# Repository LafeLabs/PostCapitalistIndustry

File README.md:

#   Theory and Practice of Trash Magic

### Lafe Spietz 2016

[Intellectual Property Notice("license")](intellectual_property_notice.md)

[Bibliography](bibliography.md)

[Funding Proposal](heilmeier_catechism_lafelabs.md)

[Demo List](demo_list.md)

[Glossary List](glossary_terms.md)

[Format Notes](format_notes.md)

[Technical Roadmap](technical_roadmap.md)

[Purpose of Book 1](purpose_book1.md)

[Illustrations for Book I](illustrations_for_book_i.md)

[3d files for volume 1 ](3dfilesVolume1List.md)

[videos for volume 1 ](videos.md)

### Book 1. Philosophy of Trash Magic: Ways of Witchery and Wizardry

1. [What is capitalism?](capitalism.md)
2. [What is free technology?](free_technology.md) 
3. [Statement of Principles](Principles.md)
4. [What is Trash Magic?](what_is_the_trash_wizard.md)
5. [taking over the universities](universities.md)
6. [Rumbles of Robots](RumblesRobots.md)
7. [Free Drugs, SlimeZistors, and Ion Magic](slimeTechPolitical.md)
8. [Magic Tales and Magic Lore](value_circles_economics.md)
9. [The Great Junk Car Feed](JunkCars.md)
10. [Factories Everywhere and Nowhere](means_of_production.md) 
11. [Visions of a Better Tomorrow](visions.md)
12. [Free Everything](problems.md)
13. [Techniques](techniquesBook1.md)
14. [Let's Build This!](lets_build.md)
 
[Appendix: The Fourteen Contemplations of Manifesto](contemplations.md)

### Book 2. The Practice of Trash Magic: the Stickening

[book 2 summary](book2summary.md)

1. [Post Capitalist Industry: Trash Magic](capitalism_technical.md)
2. [Measuring the post capitalist world](Measures.md)
3. [Fear and loathing in the vector fields](Fields.md)
4. [Coils for Magnets and Motors](coils_for_magnets_and_motors.md)
5. [Motors and Pumps](MotorsPumps.md)
6. [3d Circuit Fabrication Technology from Trash](circuit_fabrication_technology.md)
7. [Rumbles of Robots](RumblesRobots.md)
8. [Energy](Energy.md) 
9. [Resonance](Resonance.md)
10. [Skeletron](skeletron.md)
11.  [Fractal Reactors and the SlimeZistor](FractalReactorSlimeZistor.md)
12. [Supply chain data structures, call to action](data_structures.md)

## Other media, volume I only

1. 3d files for each chapter, with a VR fly thru, and 3d printer files and photos with paint, also made without 3d printers(mine are hand made)
2. videos for each chapter
3. all illustrations are coloring book images
4. artifacts distributed with the book
5. documentation for tale and lore for artifacts: noise stick, vibration stick, whirligig USB charger
6. hard cover made from soft cover by hand using trash, with magic integrated into cover, fiction chapter and university chapter will have user submitted versions in different copies, there will be local variations in these.

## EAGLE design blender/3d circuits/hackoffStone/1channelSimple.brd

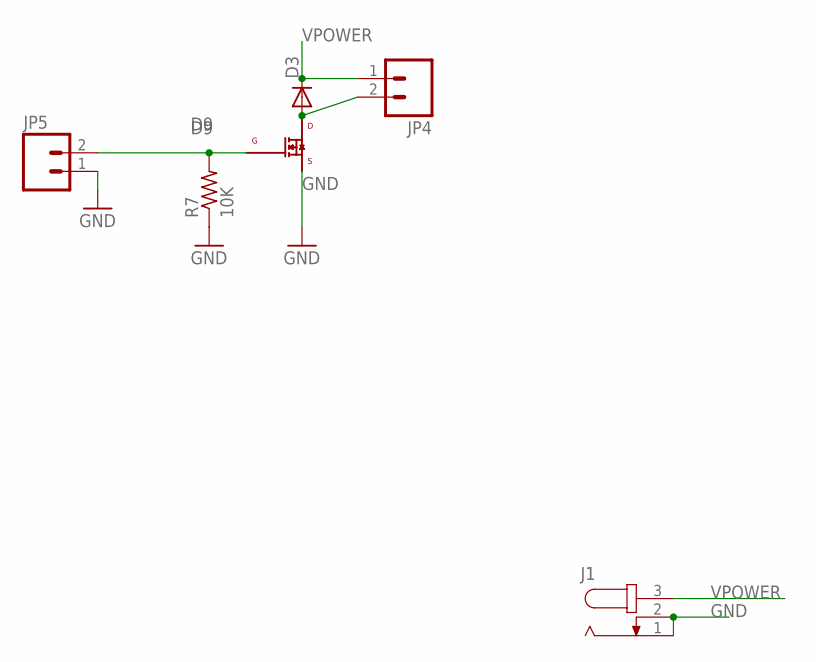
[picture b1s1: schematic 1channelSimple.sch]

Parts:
D3: DIODE-DO-214AC; DO-214AC
J1: JACK-PLUG1; SPC4078
JP4, JP5: M02PTH; 1X02
Q3: IRLML0060; SOT-23
R7: 10K; R0603

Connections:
D9: JP5.2, Q3.1 (GATE), R7.2
GND: J1.1, J1.2, JP5.1, Q3.2 (SOURCE), R7.1
unnamed: D3.A, JP4.2, Q3.3 (DRAIN)
VPOWER: D3.C, J1.3, JP4.1

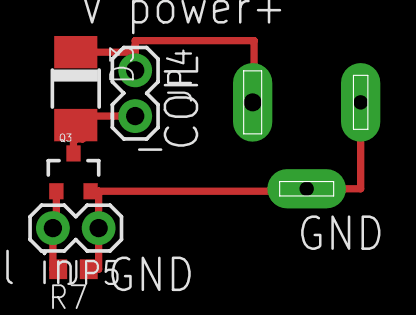
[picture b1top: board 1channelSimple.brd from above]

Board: 2 copper layers, 6 parts (1 on the bottom side), 4 nets.

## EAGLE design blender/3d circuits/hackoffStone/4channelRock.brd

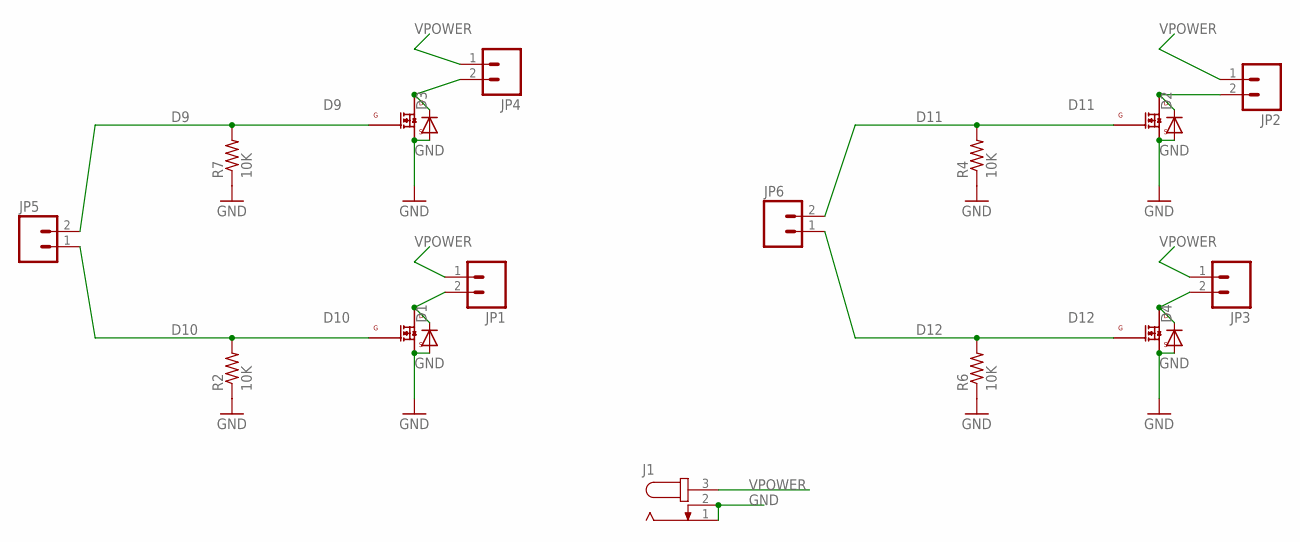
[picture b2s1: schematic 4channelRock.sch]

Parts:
D1, D2, D3, D4: DIODE-DO-214AC; DO-214AC
J1: JACK-PLUG1; SPC4078
JP1, JP2, JP3, JP4, JP5, JP6: M02PTH; 1X02
Q1, Q2, Q3, Q4: IRLML0060; SOT-23
R2, R4, R6, R7: 10K; R0603

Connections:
D9: JP5.2, Q3.1 (GATE), R7.2
D10: JP5.1, Q1.1 (GATE), R2.2
D11: JP6.2, Q2.1 (GATE), R4.2
D12: JP6.1, Q4.1 (GATE), R6.2
GND: D1.A, D2.A, D3.A, D4.A, J1.1, J1.2, Q1.2 (SOURCE), Q2.2 (SOURCE), Q3.2 (SOURCE), Q4.2 (SOURCE), R2.1, R4.1, R6.1, R7.1
unnamed: D3.C, JP4.2, Q3.3 (DRAIN)
unnamed: D1.C, JP1.2, Q1.3 (DRAIN)
unnamed: D2.C, JP2.2, Q2.3 (DRAIN)
unnamed: D4.C, JP3.2, Q4.3 (DRAIN)
VPOWER: J1.3, JP1.1, JP2.1, JP3.1, JP4.1

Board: 2 copper layers, 19 parts (0 on the bottom side), 10 nets, no tracks yet.

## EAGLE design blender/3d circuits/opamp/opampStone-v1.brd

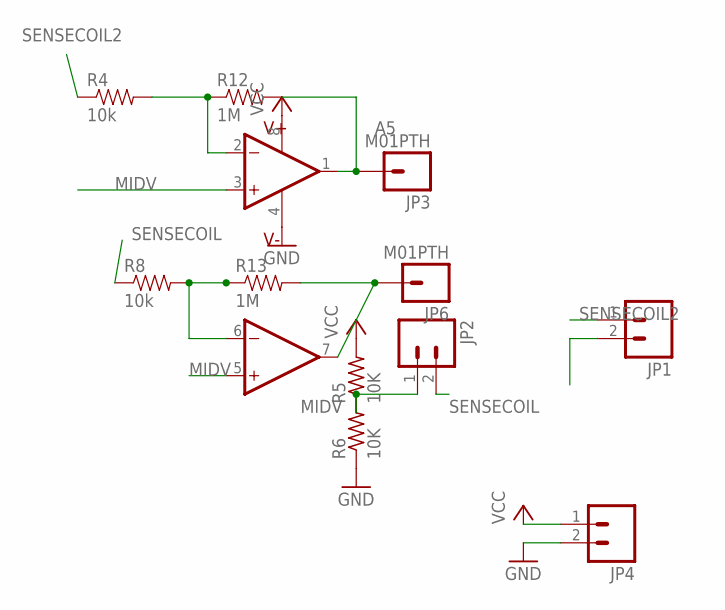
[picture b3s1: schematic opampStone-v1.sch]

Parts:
JP1, JP2, JP4: M02PTH; 1X02
JP3, JP6: M01PTH; 1X01
R4, R8: 10k; 0603-RES
R5, R6: 10K; R0603
R12, R13: 1M; 0805
U2: MCP6242; 8-SOIC

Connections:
A4: JP6.1, R13.2, U2.7 (OUTB)
A5: JP3.1, R12.2, U2.1 (OUTA)
GND: JP4.2, R6.1, U2.4 (V-)
MIDV: JP1.2, JP2.1, R5.1, R6.2, U2.3 (+INA), U2.5 (+INB)
unnamed: R4.2, R12.1, U2.2 (-INA)
unnamed: R8.2, R13.1, U2.6 (-INB)
SENSECOIL: JP2.2, R8.1
SENSECOIL2: JP1.1, R4.1
VCC: JP4.1, R5.2, U2.8 (V+)

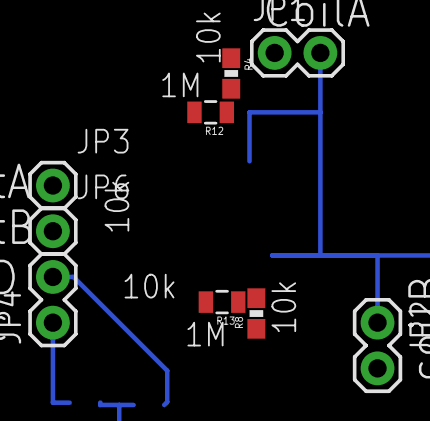
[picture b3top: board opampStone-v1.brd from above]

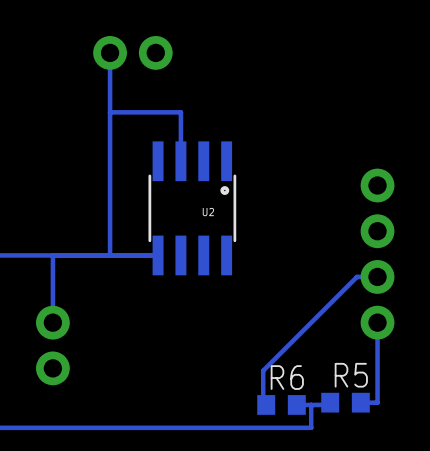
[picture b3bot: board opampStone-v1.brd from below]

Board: 2 copper layers, 12 parts (3 on the bottom side), 9 nets.

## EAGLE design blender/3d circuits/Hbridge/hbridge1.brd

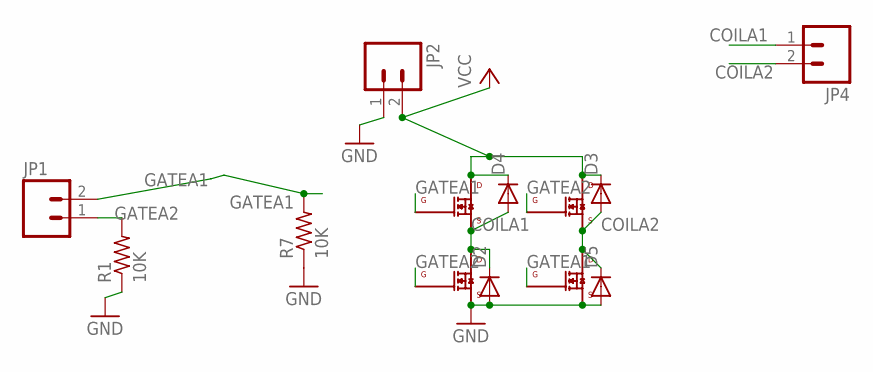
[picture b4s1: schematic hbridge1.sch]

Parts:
D2, D3, D4, D5: DIODE-DO-214AC; DO-214AC
JP1, JP2, JP4: M02PTH; 1X02
Q2, Q3, Q4, Q5: IRLML0060; SOT-23
R1, R7: 10K; R0603

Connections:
COILA1: D2.C, D4.A, JP4.1, Q2.3 (DRAIN), Q4.2 (SOURCE)
COILA2: D3.A, D5.C, JP4.2, Q3.2 (SOURCE), Q5.3 (DRAIN)
GATEA1: JP1.2, Q4.1 (GATE), Q5.1 (GATE), R7.2
GATEA2: JP1.1, Q2.1 (GATE), Q3.1 (GATE), R1.2
GND: D2.A, D5.A, JP2.1, Q2.2 (SOURCE), Q5.2 (SOURCE), R1.1, R7.1
VCC: D3.C, D4.C, JP2.2, Q3.3 (DRAIN), Q4.3 (DRAIN)

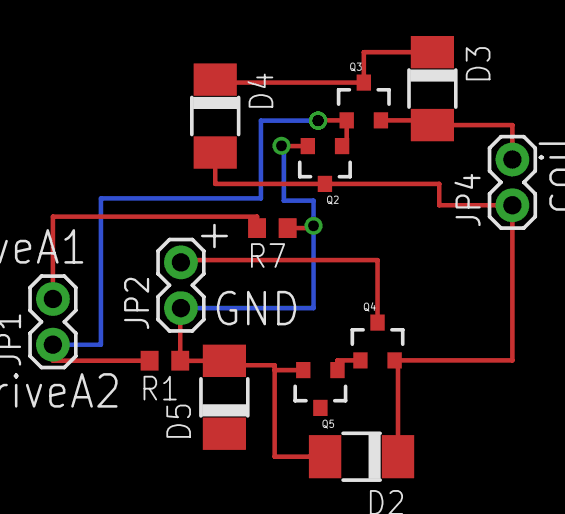
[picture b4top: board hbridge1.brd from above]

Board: 2 copper layers, 13 parts (0 on the bottom side), 6 nets.

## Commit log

2016-02-04 Update README.md
    add table of contents, with link to first chapter
2016-02-04 Update README.md
    capitalization of capitalism
2016-02-04 Moved all the python notebooks over
    from the cloud drive to the desktop git folder, trying to do this git
    thing again for real
2016-02-04 added cut and paste to capitalism chapter
2016-02-04 Rename Filelds.md to FileldsChapter2.md
2016-02-04 Update README.md
    added a summary of trash wizardry
2016-02-05 added cartoons of fractal reactor
2016-02-05 Update README.md
    add link to fractal reactor chamber
2016-02-07 added image dir
2016-02-07 added cartoon of conical stick joint
2016-02-07 cone hole fig
2016-02-07 added anarchist black cat logo from wikipedia
2016-02-09 worked on the book and logo shit
2016-02-09 move everything around, add main.md
2016-02-09 editing the whole book
2016-02-09 edit the book
2016-02-10 working on the book
2016-02-10 moar edits
2016-02-10 work on the book
2016-02-11 editing
2016-02-11 figures for fields
2016-02-11 working on figures for fields chapter
2016-02-12 edits
2016-02-13 working on figures and math for figs
2016-02-14 more figure work
2016-02-14 Update fields_figures_embed.md
    remove syntax that doesnt work on github
2016-02-14 added cartoon for first pump mould insert design
2016-02-15 figures edits
2016-02-15 getting the pdf conversion set up
2016-02-15 made README file identical to main.md
2016-02-16 ball valve design
2016-02-16 changed cover image to cat with fields
2016-02-16 added cantor set cartoon
2016-02-17 added a ton of ideas about nano fabrication reactors
2016-02-19 massive updates to capitalism chapter organization
    …but just organization, minimal new content or subtracted content. Now
    the sections are about right, I think, and I just need to go find all
    the material, sort it into there, then print, re-read and re-write
2016-02-19 more updates on capitalism chapter
    trying to make it coherent, narrow focus of definition of capitalism
2016-02-20 various small updates
2016-02-21 working on wire coil physics python stuff
2016-02-21 more coil physics work in python
2016-02-21 got python scripting to work to make coils!!
    very very crude, needs tons of work, but basically can build any coil
    from a script!!!
2016-02-22 more physics analysis of current loop using Biot Savart law
2016-02-22 working on visualization of coil geometry in blender
2016-02-23 more slow work on current loop physics writeup
2016-02-23 more theory on current loop
    fixed errors, got notation more consistent, got answers consistent with
    Griffiths
2016-02-24 more plots on field stuff
2016-02-24 added a couple ideas
    1. medical imaging using permanent magnet vibrators
    2.use of plastic bottles and a heat/pressure welding tool with robotic
    arm to do 3d fabrication in a way that is much better than 3d printers.
2016-02-24 added to the plastic bottle idea
    this plastic bottle thing is the most important 3d fab technology so
    far here. It’s huge, can replace the 3d printer completely, change
    everything, plumbing, pumps, resonance, running dog robots
2016-02-24 added more about plastic bottle fabrication to Rumbles of Robots chapter
2016-02-24 added plastic bottle electrostatic motors to the motors chapter
2016-02-24 more plastic bottle insanity, plastic bottles should be everywhere!!!!!!!!
2016-02-26 everything is going like fucking gangbusters, tons of huge breakthrus
2016-02-26 added more anti-property ideas to capitalism chapter
2016-02-27 added 3d models of 3d circuit assembly, lots of blender and .stl files
2016-02-27 messed with python and data from android accelerometer
2016-02-27 3d circuit design, h bridge
2016-02-28 adding photos from documenting assembly of first 3d circuit
2016-02-28 3d circuit design
2016-02-29 topological circuit cartoon of my own format
2016-02-29 another version of 3d h bridge, better layout
2016-03-01 more 3d circuit insanity
    and it is insanity. this is insane. I need to come back to this with
    more tools.
2016-03-01 added circuit chapter
2016-03-05 changed the whole outline, FORK IN THE ROAD, it's now 2 books!1!
2016-03-05 working on the funding proposal document
2016-03-06 working on coils stuff adding specificity
2016-03-06 blender render
2016-03-06 drive coil physics
2016-03-06 more of same
2016-03-06 working on book structure, trash wizard chapter started
2016-03-06 more on the trash wizards
2016-03-07 wrapping accurate TOC into README
2016-03-07 getting the organization sharper still
2016-03-07 more shuffling of chapter content
2016-03-07 more same
2016-03-07 more metrology writing, and some small tweaks fields
2016-03-07 forked capitalism into a separate chapter for the technical work, volume II
2016-03-08 water scoop ball, started new slime tech chapter and universities
2016-03-08 3d circuit design for 4channeldriverock
2016-03-09 more 3d, updated chapters so they're all real links now, both volumes
2016-03-11 a few small edits
2016-03-11 small data structures addition
2016-03-12 skeletron 3d design
2016-03-12 skeletron 3d design, working with textures, adding basic Arduino code
2016-03-13 adding arduino programs, all untested
2016-03-13 small arduino updates, more skeletron for Trash Stick core
2016-03-13 several small edits based on brain storms
2016-03-13 IP notice
2016-03-14 added a whole bunch of stuff about industrial production in squats/occupations
2016-03-14 trash pirates, more details
2016-03-14 tiny edits, very tiny
2016-03-15 writing and stuff
2016-03-16 added huge section to trash magic economics about post capitalist sex industry
2016-03-16 small additions to principles list
2016-03-16 fractal fasteners concept for skeletron
2016-03-18 a bunch of writing, design rules in and out of capitalism
2016-03-19 writing about measurement
2016-03-19 writing, adding tons of ideas about future
2016-03-20 added stuff from the blog, from some web research
2016-03-20 tweaking motor design in 3d rough hand
2016-03-20 tweaking motor design in 3d some more
2016-03-21 bibliography format stuff
2016-03-22 small tweaks to funding proposal
2016-03-23 3d design of simpler 1 channel and some 3d coil design
2016-03-24 lots more 3d design, re-design
    ditched the rocks, massive simplification, including the drive
    transistor into the hardware of the drive coil so that the only inputs
    are power and signal, planning to do same with sense coil and op amps.
2016-03-24 working on 3d circuit design
2016-03-24 added details to fractal reactor based on recent blog post
2016-03-27 3d design, added yale like
2016-03-28 tiny bibliography tweaks
2016-03-28 added bits about electrolytic capacitors, drive circuit schematic
2016-03-31 small tweaks
2016-04-01 website design for lafelabs
2016-04-01 lots of updates to website design
2016-04-01 website design work
2016-04-02 working on the website design
2016-04-02 changed pin numbers for buttons from 2&3 to 7&8
2016-04-03 tiny changes in stepper motor code
    still untested, but definitely ready to test, now that rotor and
    bearings are assembled.
2016-04-06 tripod!!!!!
2016-04-06 the Tripod!!!
2016-04-06 more on the trash magic stick
2016-04-07 hex motor, going from 4 to 6 coils, looking at geometry
2016-04-09 ideas about number worship as religion in capitalist philosophy
2016-04-09 more capitalist philosophy, Crowley refs
2016-04-11 op amp design tweaks
2016-04-11 working on funding stuff
    figuring out what to get funded and by whom
2016-04-13 small tweaks to book text and added DLA to funding plans
2016-04-14 python notebook updates with 27 AWG
2016-04-15 update dumb button drive
    so this should work now, 1234 or 4321 for each button push, with time
    delay T set by knob
2016-04-16 added technical roadmap
    first a list of what stages all technologies in trash magic should go
    through, then a list of technologies to be developed, divided up into
    phases.
2016-04-20 Create TempSensorBasic1
2016-04-20 Rename TempSensorBasic1 to TempSensorBasic1.ino
2016-04-23 various things
2016-04-23 sketching the motor
2016-04-24 motor sketches
2016-04-24 some details on the bioreactor technology
    probe does not need to move with sub micron precision, it’s ok to move
    the fluid with that precision *relative* to the probe instead
2016-04-24 expounded on importance of wood for plumbing
2016-04-27 small tweaks to text based on contemplations
2016-05-11 op amp design stuff
2016-05-11 added more references
2016-05-15 octal LED display using neopixels
2016-05-15 fixed various bugs, all works now :)
2016-05-25 adding to the details of what to build at the end
2016-05-26 smash all the cars
2016-05-26 added to universities some specifics
2016-05-29 figuring out what to build and how
2016-05-30 added art
2016-05-31 several updates
2016-06-02 editing for readability and accuracy
2016-06-02 making this a proper book, starting at chapter 1
2016-06-04 working on the capitalism
2016-06-04 more writing
2016-06-05 tons of edits, and figuring out tex
2016-06-05 tex! it works!
    be sure to use the compile script to turn all the .md files into .tex
    files first, and this script needs lines added as chapters are added
2016-06-05 more tex
2016-06-05 writing as well as tex formatting
2016-06-06 more work on universities chapter as well as library refs
2016-06-06 more tweaks
2016-06-06 loads of figure stuff
2016-06-07 owrkibg on writing a goddambnbook
2016-06-07 more writing and graphics
2016-06-07 writing
2016-06-07 small tweaks, adding figures to the List
2016-06-07 art, lots of art
2016-06-07 writing? i cant even remember
2016-06-07 figures and writing
2016-06-07 more writing
    switched yale case study to MIT/harvard as one unit on the Charles,
    found books on Charles river
2016-06-08 just broke 200 pages with front matter!
2016-06-08 writing lots of stuff about free stuff
2016-06-08 finished the problems chapter! and other random changes apparently
2016-06-09 re ordered chapters, wrote more on techniques chapter
2016-06-09 mostly techniques, and the usual re-compiles
2016-06-10 finished techniques section, worked on some others
2016-06-10 random
2016-06-11 turning this thing into a real book
2016-06-11 making a book
2016-06-11 universities, lots of edits
2016-06-12 lots of stuff, making 3d files and more readable stuff
2016-06-13 moving thru the book and making it readable
2016-06-13 further writing on values
2016-06-14 finished tales and lore re write!
2016-06-14 small edits
2016-06-15 3d design
2016-06-16 lots of lets build this stuff
2016-06-16 derp?
2016-06-22 lots of small edits and some 3d stuff
2016-06-24 fixed 3d by selecting all the parts this time of key
2016-06-24 moar 3d
2016-06-24 rough draft of all 14 files now done!
2016-06-25 the 14 Contemplations
2016-06-25 truncated cube
2016-06-26 vibrator design 3d stuff and also PTO
2016-06-26 made a png
2016-07-03 3d stuff
2016-07-03 contemplation graphics for coloring plates
2016-07-13 catchup
2016-07-13 finished editing first chapter!
2016-07-13 finished editing chapter 2 and also contemplation 2
2016-07-14 finished chapter 3 edits with contemplation 3
2016-07-14 finished edits and contemplation for chapter 4
2016-07-14 chapter 5 edits done, with contemplation also done
2016-07-14 finished edits on chapter 6
2016-07-15 moving thru edits fast, just finished junk cars but
    still need to do that contemplation, can leave the adding of way more
    figures for 2nd edition
2016-07-15 everything edited but last chapter and last 2 contemplations
    close! on more work session tonight and then get covers back and front
    and spine and send to printer again!!!
2016-07-16 done!!! first draft is ready for publication
2016-07-16 changed front cover to right format for lulu
2016-07-16 made a html home page for the project

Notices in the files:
parts and their libraries:
SparkFun-Connectors: Licensing: Creative Commons ShareAlike 4.0 International - https://creativecommons.org/licenses/by-sa/4.0
SparkFun-Passives: Licensing: CC v3.0 Share-Alike You are welcome to use this library for commercial purposes.
